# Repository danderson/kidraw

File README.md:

# Kidraw

Kidraw is a library to programmatically build Kicad schematic and
footprint libraries. It was created out of frustration with Kicad's
inconsistent built-in libraries, and the tedium of building cookie
cutter parts in the library editors.

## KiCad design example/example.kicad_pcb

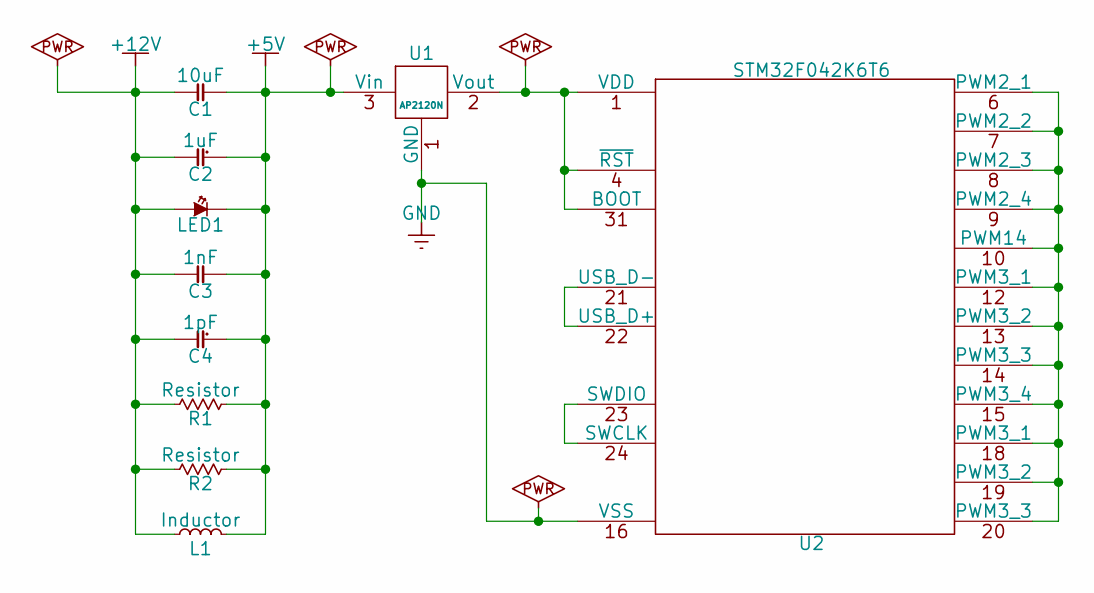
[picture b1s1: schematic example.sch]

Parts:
C1: 10uF; Capacitor_0603
C2: 1uF; Capacitor_(Polarized)_1206
C3: 1nF; Capacitor_1206
C4: 1pF; Capacitor_(Polarized)_0805
L1: Inductor; Inductor_1206
LED1: LED; LED_1206
R1: Resistor; Resistor_0805
R2: Resistor; Resistor_1206
U1: AP2120N; AP2120N_SOT23-3
U2: STM32F042K6T6; STM32F042K6T6_32-QFP

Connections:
+5V: C1.2, C2.2, C3.2, C4.2, L1.2, LED1.2, R1.2, R2.2, U1.3 (Vin)
+12V: C1.1, C2.1, C3.1, C4.1, L1.1, LED1.1, R1.1, R2.1
GND: U1.1 (GND), U2.16 (VSS), U2.32 (VSS)
unnamed: U2.6 (PWM2_1), U2.7 (PWM2_2), U2.8 (PWM2_3), U2.9 (PWM2_4), U2.10 (PWM14), U2.12 (PWM3_1), U2.13 (PWM3_2), U2.14 (PWM3_3), U2.15 (PWM3_4), U2.18 (PWM3_1), U2.19 (PWM3_2), U2.20 (PWM3_3)
unnamed: U2.21 (USB_D-), U2.22 (USB_D+)
unnamed: U2.23 (SWDIO), U2.24 (SWCLK)
VDD: U1.2 (Vout), U2.1 (VDD), U2.4 (~RST), U2.5 (VDD), U2.17 (VDD), U2.31 (BOOT)

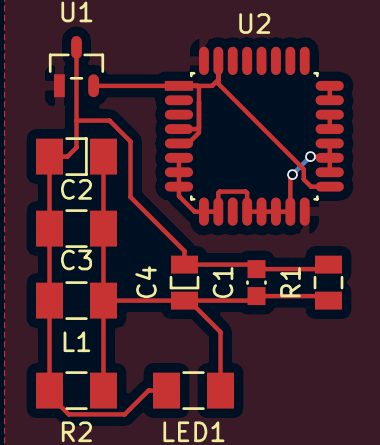
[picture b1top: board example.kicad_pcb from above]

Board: 2 copper layers, 10 parts (0 on the bottom side), 7 nets.

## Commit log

2015-11-08 Initial import
2015-11-08 Checkpoint while hacking - basic IC layout seems to work.
2015-11-09 Implement a good enough IC layout algorithm.
2015-11-09 Correct the electrical type for ground and the power flag.
2015-11-09 Add license and .gitignore.
2015-11-15 Rewrite kidraw to a different DSL style.
2015-11-15 Port stdlib to the new library.
2015-11-16 Add an IC builder - still a bit buggy.
2015-11-17 3to2-ify kidraw.
2015-11-17 Fix spurious offsets in IC builder.
2015-11-17 Fix 3to2 bugs.
2015-11-18 Fix power and IC pin drawing.
2015-11-18 Fix power symbols in the stdlib.
    Kicad uses the pin name in power symbols as the net name that
    the symbol represents. The stdlib symbols had no pin name,
    which massively confused the ERC.
2015-11-18 Bump package version to 2.
2015-11-18 Add a footprints standard library.
    Currently only defines a couple of SMD 2-terminal footprints.
2015-11-19 Fix some module rendering issues for footprints.
2015-11-22 Yet another rewrite, concentrating on IPC footprints for now, then back-expanding back to schematic.
2015-11-22 Add documentation to various methods.
2015-11-22 Switch all docstrings to dquotes.
2015-11-22 Remove extra dash from the standard name.
2015-11-24 Start implementing footprint drawing.
    Can currently do chip-style components and dual/quad-in-line.
2015-11-24 Scale SVG output better, and add courtyard margins.
2015-11-24 Fix incorrect assembly layer pin drawing for quad-in-line devices.
2015-11-24 Use symbolic PenWidth constants instead of hardcoding 0.15.
    Also takes the opportunity to thin out assembly layer traces here,
    which looks a bit prettier and makes the silkscreen more obvious.
2015-11-24 Make the bounding_box method public.
2015-11-25 Refactor drawing logic, fix some display bugs.
2015-11-25 Add a footprints "report card".
2015-11-25 Invert square and obround pad drawing to make square the default.
2015-11-26 Tweak drawing output to be a little bit prettier.
2015-11-26 Report infeasible designs when pads overlap.
    So far, I've only encountered this with one molded capacitor part when
    using the "most" size profile.
2015-11-26 Refactor the test card to show infeasible components.
2015-11-26 Add SOPJ footprints to the test card.
    These footprints triggered some bugs in silkscreen outline drawing.
    Now, if pads protrude over the corners of the component outline
    silkscreen, the whole silkscreen is pulled into within the pads.
2015-11-26 Attempt to rationalize assembly pin drawing.
    The drawing is still ugly and unmaintainable. The true solution is
    going to be to do transform-based drawing.
2015-11-26 Redo silkscreen drawing for in-line pin footprints.
2015-11-26 Fix drawing tests, now that we're drawing what we want.
2015-11-26 Reduce the size of the pin 1 marker slightly.
2015-11-26 Add a MELF footprint to the inspection card.
2015-11-26 Move the pin renderer out into a standalone helper.
2015-11-26 Add SOT23-3 and SOT23-5 builders.
2015-11-26 Make kidraw.ipc into a directory package, in prep for adding subpackages.
2015-11-26 Add a reference library to generate chip device patterns.
    The patterns use dimensions taken from Vishay. Annoyingly, there seems
    to be no standard for the termination sizes or tolerances for chip
    devices, so it comes down to a random choice between manufacturers.
2015-11-27 Make IPC footprint importer a method of Footprint.
2015-11-27 Move IPC test into the subpackage.
2015-11-28 Port the schematic library back from the previous iteration.
2015-11-28 Reimplement the main kidraw library, which just ties all the other things together.
2015-11-28 Various renaming and tidying up, while attempting to make the whole thing presentable.
2015-11-28 Make schematic and footprint into full packages.
    The intent is to add the libraries of each type as subpackages.
2015-11-28 Start using golden-based unit tests for the IPC library.
2015-11-28 Golden tests for imperial chips.
2015-11-28 Add golden test for SOIC.
2015-11-28 Add test for *SOP.
2015-11-28 Add tests for SOT23... And fix numerous bugs about them :).
2015-11-28 Add test for QFP.
2015-11-28 Add test for QFN builder (and fix bug in said builder).
2015-11-28 Add non-IPC footprint library.
    This is just a straight translation of the IPC land pattern generators
    into Kicad footprint library.
2015-11-28 Remove the solder mask margin, so that users can set their own.
    The mask margin is usually set as a function of the fab you're
    sending designs to, so the library shouldn't be opinionated by
    default. Kidraw users can still set it by hand on the generated
    footprints.
2015-11-28 Rename footprint_test.py so that Nose2 can find it.
2015-11-28 Fix up the test card generator.
2015-11-28 Simplify the test card generator using the IPC library.
2015-11-28 Add don't-care pins to the schematic as hidden elements.
    This will let Kicad correctly match up schematics and viable
    footprints, without cluttering up the schematic with unused
    pins.
2015-11-28 Move the test card generator to the root of the project.
2015-11-28 Move the schematic library into a separate package.
2015-11-28 Remove the examples folder.
2015-11-28 Minor tweaks to schematic building, as I write an example project.
2015-11-28 More bugfixes and tweaks resulting from building the sample project.
2015-11-28 Add an example project.
    The actual schematic and wiring is nonsensical, it exists only to
    show off the schematic components and footprints.
2015-11-29 Add SC70 (JEDEC MO-203) footprints to the IPC library.
    SC70 is a well-behaved JEDEC footprint, so it makes for a trivial
    builder.
2015-11-29 Fix tests following implementation of footprint text placement.
2015-11-29 Redraw goldens following implementation of footprint text placement.
2015-11-29 Add SC70 footprint to the footprint library.
2015-12-02 Add a test point footprint.
2015-12-02 Tweak aspect ratio correction.
2019-09-13 Dump all the random stuff I changed before stopping development.
2024-05-05 add temporary(?) dev setup
2024-05-05 get poetry set up
2024-05-05 more poetry setup
2024-05-05 Fix over one thousand ruff lint reports.
2024-05-05 Fix up some more lint errors
2024-05-05 Adjust ruff linting
